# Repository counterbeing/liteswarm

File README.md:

## 2023-09-08 NOTE
this branch is a merge from a separate repo 100ideas/scarfswarm/releases/tag([BM23](https://github.com/100ideas/scarfswarm/releases/tag/BM23)|[v0.1.0](https://github.com/100ideas/scarfswarm/tree/v0.1.0)) which itself was refactored from [the 2019-july master branch of this  repo counterbeing/liteswarm, somewhere around here](https://github.com/counterbeing/liteswarm/blob/dc4e0e53ea9b77c02f954a00a81d340e21b89678/src/main.cpp). This branch compiles on esp32 dev boards with nrf24 and rotary encoder knobs attached to esp32 GPIO pins as defined in [`/src/config.h`](src/config.h). 

The GPIO pin settings should be compatible with ESP-WROOM-32 DevKit-v1 style breakout boards. I used these "[5PCS ESP-WROOM-32 ESP32 ESP-32S Development Board...](https://www.amazon.com/dp/B0BK13HWBJ) from amazon, but I want to switch to using one of the boards made by [Unexpected Maker](https://unexpectedmaker.com/shop.html) (tbd)."

I forked and old commit of the master branch, back when it was reliably working on arduino teensy in july 2019, and refactored it until it worked on esp32. Note, I have not verified that it STILL works on arduino teensy, so we should add a tag to the old master at a commit that was good on teensy, maybe around here https://github.com/counterbeing/liteswarm/blob/dc4e0e53ea9b77c02f954a00a81d340e21b89678/src/main.cpp. The most recent master commit before my merge from BM23 branch was https://github.com/counterbeing/liteswarm/tree/cc187bc9ed60972e2afc4fb52d72f6577941fd4b.

I started a new repo for my development work, [100ideas/scarfswarm](https://github.com/100ideas/scarfswarm).

## about
continutation of code developed with @counterbeing in https://github.com/counterbeing/liteswarm. `BM23` (and `master` currently) branch here is a minimal refactor of the teensy/arduino-compatible master branch of the liteswarm repo from 2019. Multiple contributors attempted to refactor or rearchitect the liteswarm code for esp32 but I couldn't get any of those branches to run. This branch does run on esp32, but it is not fancy. In fact, the code is ugly. But it works. I will push it to a branch on counterbeing/liteswarm for posterity. This repo is intended to be the home of scarfswarm FOSS firmware and hardware based on esp32, contributed by 100ideas and others.

To compile and upload this code onto an ESP32, use platformio in vscode. Once the platformio extension is activated, it should automagically configure a local gcc toolchain, download the project dependencies (`fastled/FastLED@^3.5.0`, `dparson55/NRFLite@^3.0.3`, `madhephaestus/ESP32Encoder`, `thomasfredericks/Bounce2@^2.55`, and all the magic contained in the `framework = arduino` line of `platformio.ini`), and compile them for esp32. If you encounter trouble building, try disabling `gcc` warnings by using a `platform.ini` similar to below (specifically `build_unflags` line):
```ini
[env:esp32dev]
platform = espressif32
board = esp32dev
framework = espidf
upload_port = /dev/cu.SLAB*
monitor_port = /dev/cu.SLAB_USBtoUART
monitor_speed = 115200
; esp32_exception_decoder is an add-on that parses kernel panic messages on serial such that error codes
;   and memory locations / program counter numbers are replaces with src code coordinates - handy!
monitor_filters = default, esp32_exception_decoder
; fix vendor-default extreme error setting in GCC (example code won't compile)
;   by disabling all gcc warnings
;   https://community.platformio.org/t/disable-warning-errors/13280/3
build_unflags = -Werror=all
; in extreme cases you may need to mess with how the linker/compiler resolves dependencies, try:
; lib_ldf_mode = chain+
```

**END 2023-09-08 NOTE**
---

## Swarming LEDs for LED Fun
This project can be be applied to many projects. Our prototype has been in scarves. These can also go in all sorts of other places:

- Wearables such as scarves and hats.
- Bike safety helmet.
- Bike lights.

### Why these? What's the swarm?
The thing that makes this project unique is the swarm. We're working to establish a way for multiple projects to communicate so that you can sync up animations with friends or even strangers.

Cheap simple hardware that can be put together in a robust and ad-hoc way to
keep you safe for nights of partying, or bicycling. Keep your friends all in a group with a synchronized mobile light show.

### Materials / Shopping List
These are some of the materials we've used to build our own. You can pretty much bank on them workin for your project.
- [portable battery packs](https://smile.amazon.com/Smallest-Jackery-3350mAh-Portable-Charger/dp/B00L9F95RO/ref=sr_1_8?keywords=jackery+battery+pack&qid=1559954560&s=gateway&sr=8-8), not a bad idea to have two. These are small enough to fit inside of a fuzzy scarf, and they don't turn off on you. You can get a few hours out of one of these... Depends on the animation you run. *mac likes Jackery if you can find 6000-12000mAh capacity for less than $20)
- another batt option [PowerAdd Slim 2 5000 mAh Compact Battery Packs](https://www.amazon.com/dp/B00KG45W08) ($13)
- [fabric](https://www.joann.com/luxury-faux-husky-fur-fabric--white/14387674.html)
- [arduino nanos](https://smile.amazon.com/gp/product/B07HF5RMHV/ref=crt_ewc_title_dp_2?ie=UTF8&psc=1&smid=A278BT9THV444Y)
- [led strips](https://www.aliexpress.com/item/5m-5V-WS2812B-WS2812-Led-Strip-light-Individually-Addressable-Smart-RGB-Led-pixel-strips-Black-White/32995915537.html?spm=a2g0o.cart.0.0.69a03c00Io4CfT)
- moar strips [WS2811](https://hackmd.io/@100ideas/scarfswarm#LED-strips) (see hackmd doc below for links to Ray Wu's led store)
- [usb cables](https://www.amazon.com/HTTX-Straight-Soldering-Connector-Replacement/dp/B07D1HDJM8/ref=sr_1_10?keywords=usb-a+connector+male&qid=1559956539&s=gateway&sr=8-10)
- [rotary encoder](https://smile.amazon.com/DIYhz-Rotary-Encoder-Digital-Potentiometer/dp/B07D3D64X7/ref=sr_1_10?keywords=rotary+encoder&qid=1559955080&s=industrial&sr=1-10)
- [wire](https://www.amazon.com/StrivedayTM-Flexible-Silicone-electronic-electrics/dp/B01KQ2JNLI/ref=sr_1_8?keywords=soldering+wire&qid=1559956794&s=gateway&sr=8-8)
- [nRF24L01+ 2.4 Ghz radio](http://a.co/d/3rhLgCT)
- Bourns PEC11 12mm 24-pulse rotary encoder (PEC11-4215F-S24) [adafruit #377](https://www.adafruit.com/product/377) ($4.50/1); [datasheet](https://cdn-shop.adafruit.com/datasheets/pec11.pdf) (need 10x)
- [usb type a male adapter 20-pack]( https://www.amazon.com/gp/product/B07GGJGB7Q) ($11) (for making power cables)
- [JST 4pin male-female connector pigtails, pack of 20](https://www.amazon.com/gp/product/B075K3M1TB) ($11)
- [112Pcs 2.54mm Male and Female Pin Header Connector Assortment Kit, 100pcs Stackable Shield Header](https://www.amazon.com/gp/product/B07CWSXY7P) ($13)
- [Capri Tools 20011 Automatic Wire Stripper and Cutter
](https://www.amazon.com/gp/product/B01018CX46) ($14) - get one. changed my life.

[
Scarfswarm / bikelights Big Red animation demo (youtube 2m)](https://youtu.be/5sAtdrZpyJc)

## Contributing
### Getting Involved
If you'd like to submit a bug, go ahead and use the issue tracker.

If you'd like to make submit a feature or a fix.
  - Open an issue to get buy in.
  - Fork the repo.
  - Make your changes.
  - Submit a pull request.

### Troubleshooting
Things you might be missing.
- edit using VSCode with PlatformIO plugin
- OpenOCD some USB stuff `brew install openocd` (or else `dyld: Library not loaded: /usr/local/opt/libftdi/lib/libftdi1.2.dylib`)

## Reference
**project documentation** https://hackmd.io/@100ideas/scarfswarm

libraries we're using:
- [FastLED.h](https://github.com/FastLED/FastLED) let their be light
- [NRFLite.h](https://github.com/dparson55/NRFLite) ... longwave light
- arduino / teensy [SPI](https://www.pjrc.com/teensy/td_libs_SPI.html) library
- [Encoder](https://github.com/PaulStoffregen/Encoder) - performant quadrature encoder for rotary inputs
- 

---

## 2019-12-12 Teensy-LC + NRF24L01+ notes

teensy forum faq: https://forum.pjrc.com/threads/25395-Teensy-Quick-Reference-Code-Examples-Tips-and-Tricks?highlight=nrf24l01
- also see
  - getting 128-bit ID hardcoded into chip
  - interval timer using interrupts
  - simple task library
  - libs https://www.pjrc.com/teensy/td_libs.html
    - debounce
    - timers

Optimized High Speed NRF24L01+
- https://tmrh20.github.io/RF24/
- mentioned on pjrc forums https://forum.pjrc.com/threads/40499-Need-to-change-SPI-clock-rate-for-RF24-radio-modules-w-TMRh20-library

NRF24L01+ w/ amazon breakout boad diagram
-----------------------------------------------------------------------------------------------

                                                 (pins)       NRF24L01+ breakout board pcb
    | nrf:teensy pin# | nrf:teensy     |      |-----------------------------------------------|
    | --------------- | -------------- |      |[1] | 2  |                      (antenna)      |
    | 1: GND   GND    | 2: VCC  (+3.3v)|      | -- | -- |        -------     ===============  |
    | 3: 9     CE     | 4: 10?  CSN    |      | 3  | 4  |        | C H |        ||   -----||  |
    | 5: 13    SCK    | 6: 11   MOSI   |      | -- | -- |        | I P |        ||   ||-----  |
    | 7: 12    MISO   | 8: ?    IRQ    |      | 5  | 6  |        -------        ||   -----||  |
                                              | -- | -- |                       ||   ||-----  |
                                              | 7  | 8  |                       ||   -----||  |
    Functions as follows:                     |---------|                            ||-----  |
    1: Ground                                 |         ( 16.000 )                        ||  |
    2: Vcc (3.3v)                             |-----------------------------------------------|
    3: CE (Chip Enable)
    4: CSN (Chip Select Not) Active Low - SPI Chip Select function
    5: SCLK (Clock) - SPI Clock Function
    6: MOSI (Master Out Slave In) - SPI Data
    7: MISO (Master In Slave Out) - SPI Data
    8: IRQ (Interrupt) - Optional, but goes low to indicate that data has arrived, fault has
       occurred, or write buffer full.

> SPI has 4 signals: **SS**, **SCK**, **MOSI**, **MISO**. SCK is a clock signal. Master Out Slave In (MOSI) sends data from the SPI master to one or more slaves. Master In Slave Out (MISO) is how slaves send data back to the master. To talk to only one of several slaves, the Slave Select (SS) pin is used. Thus, some chips need only 3 or even 2 of these signals; a display, for example, will use MOSI but not MISO, as it is an output only device.
>
> Multiple SPI devices use the same SPI SCK, MISO and MOSI signals but each device will need it's own SS pin.

| Signal | Function      | Teensy 2.0 | Teensy++ 2.0 | Teensy 3+ / LC * | ALT Teensy 3+ / LC |
| ------ | ------------- | ---------- | ------------ | -------------- | ------------------ |
| SS     | Select device | 0          | 20           | 10             | -                  |
| SCK    | Clock         | 1          | 21           | 13             | 14                 |
| MOSI   | Data Output   | 2          | 22           | 11             | 7                  |
| MISO   | Data Input    | 3          | 23           | 12             | 8                  |

\* these pins are set by default by SPI library(?). To use ALT, make calls to `SPI.setMOSI(pin)` etc.

> However, the SS pin must either be configured as an output, or if it is an input, it must remain low during the SPI transfer. Unconfigured pins default to input, and a pin with no signal can easily "float" to random voltages due to electrical noise. Always configure the SS pin as an output, or make sure it remains low.
>
> Sometimes, the SPI pins are already in use for other tasks when an SPI device is added to a project. If that task is simply a digital pin, or an analog input, it is usually better to move that to another pin so that the hardware SPI can be used. Sometimes though, the conflicting pin cannot be moved. The Audio Adapter, for example, uses some of the SPI pins to talk to the Audio DAC over I2S. For this case, Teensy 3.x provides an alternate set of SPI pins.
>
> The main SPI pins are enabled by default. SPI pins can be moved to their alternate position with SPI.setMOSI(pin), SPI.setMISO(pin), and SPI.setSCK(pin). You can move all of them, or just the ones that conflict, as you prefer. The pin must be the actual alternate pin supported by the hardware, see the table above; you can't just assign any random pin.

https://www.pjrc.com/teensy/td_libs_SPI.html

-----------------------------------------------------------------------------------------

## dont overflow if counting packets...
how many packets (max) could a device see per second?
```
(800kbps * 1 second) / 32 bytes = 3125
(2MBps * 1 second) / 32 bytes   = 62500
```
see UINT_MAX from std::numeric_limits 
- https://en.cppreference.com/w/cpp/types/climits
- https://en.cppreference.com/w/cpp/types/integer

| uint sizes | atmel / arduino | teensylc arm cortex M0 |
| ---------- | --------------- | ---------------------- |
| INT8_MAX   | 127             |                        |
| UINT8_MAX  | 255             |                        |
| INT16_MAX  | 32767           |                        |
| UINT16_MAX | 65535           |                        |
| INT32_MAX  | 2147483647      |                        |

```c
// https://www.badprog.com/c-type-what-are-uint8-t-uint16-t-uint32-t-and-uint64-t

// testValue
unsigned long long testValue     = 0xFFFFFFFFFFFFFFFF; // 18446744073709551615

// 1 byte -> [0-255] or [0x00-0xFF]
uint8_t         number8     = testValue; // 255
unsigned char    numberChar    = testValue; // 255

// 2 bytes -> [0-65535] or [0x0000-0xFFFF]
uint16_t         number16     = testValue; // 65535
unsigned short    numberShort    = testValue; // 65535

// 4 bytes -> [0-4294967295] or [0x00000000-0xFFFFFFFF]
uint32_t         number32     = testValue; // 4294967295
unsigned int     numberInt    = testValue; // 4294967295

 // 8 bytes -> [0-18446744073709551615] or [0x0000000000000000-0xFFFFFFFFFFFFFFFF]
uint64_t             number64         = testValue; // 18446744073709551615
unsigned long long     numberLongLong    = testValue; // 18446744073709551615
```

## deviceId collisions
calculate liklihook of id collisions, where n = number of devices & d = keyspace size (using birthday problem formula):

1 - (d!) / ((d - n)! * d^n)

n = 10 devices
d = 256 (uint_8)
p = 16%

n = 10 devices
d = 32768 (uint_16)

### 2019-11-21 dev notes for scarfquest
intellisense not picking up uintxx types from `/Users/100ideas/.platformio/packages/toolchain-atmelavr/avr/include/stdint.h`

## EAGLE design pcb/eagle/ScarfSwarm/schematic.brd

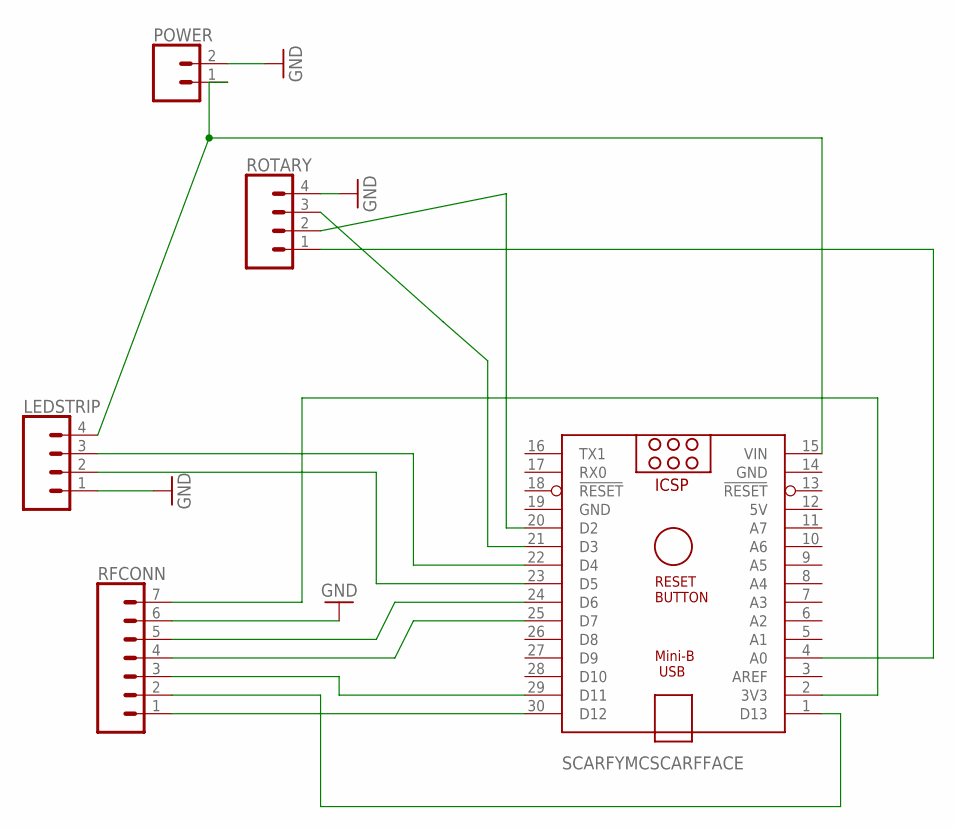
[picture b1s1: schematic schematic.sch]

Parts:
LEDSTRIP: CONN_04PTH; 1X04
POWER: CONN_02LOCK_LONGPADS; 1X02_LOCK_LONGPADS
RFCONN: CONN_07; 1X07
ROTARY: CONN_04PTH; 1X04
SCARFYMCSCARFFACE: ARDUINO_NANO

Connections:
5V: SCARFYMCSCARFFACE.12 (5V)
GND: LEDSTRIP.1, POWER.2, RFCONN.6, ROTARY.4, SCARFYMCSCARFFACE.14 (GND), SCARFYMCSCARFFACE.19 (GND)
unnamed: RFCONN.7, SCARFYMCSCARFFACE.2 (3V3)
unnamed: RFCONN.5, SCARFYMCSCARFFACE.24 (D6)
unnamed: RFCONN.4, SCARFYMCSCARFFACE.25 (D7)
unnamed: RFCONN.2, SCARFYMCSCARFFACE.1 (D13)
unnamed: RFCONN.3, SCARFYMCSCARFFACE.29 (D11)
unnamed: RFCONN.1, SCARFYMCSCARFFACE.30 (D12)
unnamed: LEDSTRIP.2, SCARFYMCSCARFFACE.23 (D5)
unnamed: ROTARY.3, SCARFYMCSCARFFACE.21 (D3)
unnamed: ROTARY.2, SCARFYMCSCARFFACE.20 (D2)
unnamed: ROTARY.1, SCARFYMCSCARFFACE.4 (A0)
unnamed: LEDSTRIP.4, POWER.1, SCARFYMCSCARFFACE.15 (VIN)
unnamed: LEDSTRIP.3, SCARFYMCSCARFFACE.22 (D4)

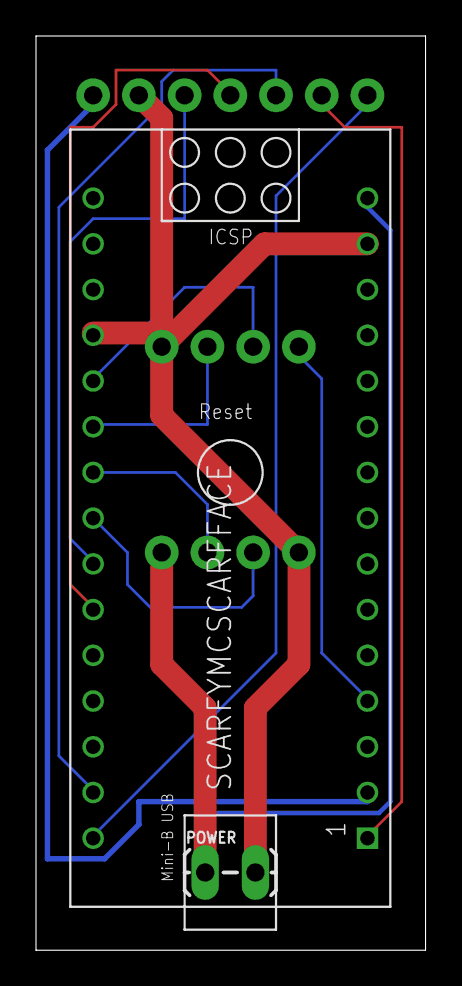
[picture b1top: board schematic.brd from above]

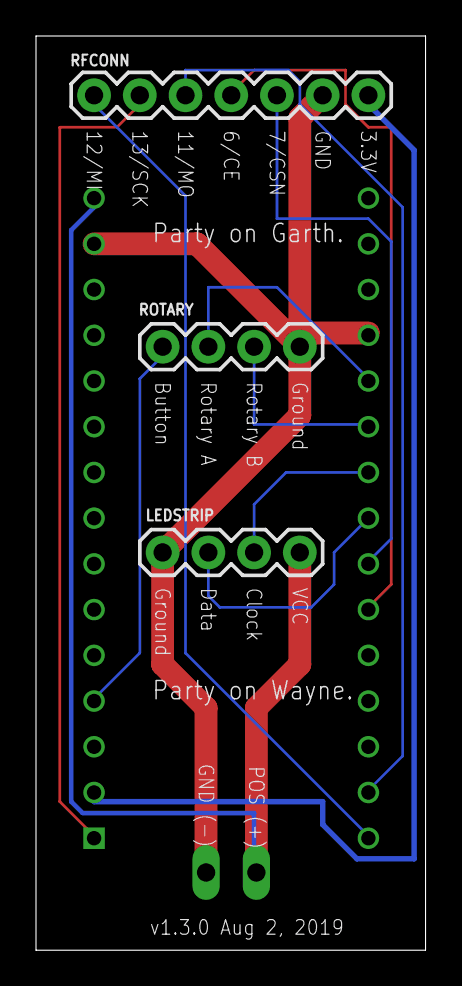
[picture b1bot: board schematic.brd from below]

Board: 2 copper layers, 21.6 x 50.8 mm, 5 parts (3 on the bottom side), 13 nets.

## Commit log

2016-08-07 initial working
2016-08-07 add debouncer
2016-08-08 reading rotary
2016-08-08 adjust animation speeds
2016-08-08 add some animations
2016-08-15 performance adjustments
2016-08-15 unblock strobe call
2016-08-16 add crossfade back in
2016-08-25 add snakes on a plane
2017-09-08 playa hacks to strandtest.ino for longer lengths
2017-09-08 add documentation folder
2017-09-09 pinouts & datasheets
2019-06-06 trying out an ide
2019-06-07 reorder some things
2019-06-07 got it compiling and uploading
2019-06-07 code is messed up, updates to readme
2019-06-07 problematic
2019-06-07 reg error
2019-06-07 this compiles with knob logic extracted to h file
2019-06-07 tweakls
2019-06-07 tinker
2019-06-07 kind of working... with mac
2019-06-07 closer to working
2019-06-07 a slightly buggy branch
2019-06-07 remove unnecessary variable from circulation
2019-06-07 some kinda fix, whew, we tired
2019-06-07 Things are working as of now.
    - Removed Serial comments
    - Race now does what color slide once did
    - Color slide is no longer included as it was buggy
    - No plans to reimplement race as it was originally, never really liked
    it all that much.
2019-06-07 Cleanup.
    - Added debugging note
    - Removed stale comments and code
    - Adjusted pixel value using debug technique
    We could potentially stick that NUMPIXELS into an env var or something,
    but for now, it's here.
2019-06-08 Add list of materials
2019-06-08 Added a new animation to choose your own color
2019-06-08 color chooser doesn't quite work for some reason
2019-06-08 It's in working order, but no color chooser
    Interestingly there are problems if i change the order of the case
    statement, I have no idea why.
2019-06-16 Added looping ability.
    This is mostly for color chooser, which still causes some kind of other
    crash. Still working that out, if you want to try it out feel free to
    comment out the switch statment and just run the color chooser
    animation.
2019-06-17 moved basic animation to class
2019-06-17 knob receives defaults from animation instance
2019-06-17 added crossfade back in
2019-06-17 diamond necklace runs as intended
2019-06-17 added fuck my eyes
2019-06-17 major cleanup
2019-06-17 dotstar lib is now gone
2019-06-17 moving animations to folder and more cleanup of old vars
2019-06-17 Use pointers to reference animations
    Rather than using the run function directly from the instance of the
    animation, we use a pointer. This allows us to call the setup function
    once for each animation without repeating it over and over.
2019-06-17 tweaks and cleanup
2019-06-17 for whatever reason this order works, not sure why
2019-06-17 slightly faster defualt intervals for a couple of animations
2019-06-19 temp change to ws2811
2019-06-22 very literal move of code not working yet
2019-06-23 almost working basic RF
2019-06-23 this works
2019-06-23 keyframe note
2019-06-26 these sync with animation and rotary
2019-07-08 Fixes for jittery changes when using rotary
    Previously all parties tried to broadcast constantly, this could turn
    into a feedback loop. Here we prevent the broadcast of a packet unless
    there is a manual change that needs broadcasting.
    Also add a sync period.
2019-07-26 with rainbow animation
2019-07-26 add initial schematic
2019-07-26 try trimming off th external componetns, first board layout
2019-07-27 add auto routing with pads on back
2019-07-28 swapped out arduino lib, still have errors
2019-07-28 add libs
2019-07-30 v1 of boards
2019-07-30 add a little more beef to some of the power lines
2019-07-30 v1.1 Fatten some of the leads
2019-07-31 scarfymcscarfface
2019-07-31 silk screen change
2019-08-02 reorder radio contacts so that they are easy to solder
2019-08-02 tidy schematic slightly
2019-08-02 remove old backup
2019-08-06 update for PCB use
2019-08-06 rearrange JST connection for strip, bump version
2019-08-07 reorder animations and tighten rainbow
2019-08-07 hold actions are now printed to serial
2019-08-07 code cleanup
2019-08-08 there is now an off mode
2019-08-08 add stripes animation
2019-08-08 a couple more animations
2019-08-08 clarify comment
2019-08-13 add scarf-diagram, gitignore .vscode
2019-08-13 configs for mac protoboard + breadboard
2019-08-14 partially done w/ knob combo detection
2019-08-14 think the combomatcher logic is starting to work
2019-08-14 combo logic seems good + great var names
2019-08-14 cleaned up code, looks good! next up dispatch
2019-08-14 comboPattern string -> switch case dispatcher works
2019-08-14 FIX swapped pin bug CS<->CSM v1.3; SK9822 BGR order
2019-08-14 cmdMode starts after med->short combo
2019-08-14 kinda-working off mode
2019-08-14 offmode more stable but no feedback
2019-08-14 printf.h printf() -> serial helper lib
2019-08-18 testing cedux, running out of space
2019-08-21 add ws comment
2019-08-22 change strip to WS and flip data and clock
2019-08-22 ws2815 working; clang format rule; more mem less serial
2019-08-22 updated log
2019-08-22 getting ifdefs for config.h
2019-08-22 rebased master
2019-08-22 autoformat all google clang style
2019-08-23 centralize FastLED.show()
2019-08-23 update debug var names, and update readme
2019-08-23 ignore packets without a secret
2019-08-23 do not begin transmitting immediately on launch
2019-08-23 cap brightness of dimmer to prevent 1A power source failure
2019-08-24 adding basic feedback to command mode
2019-08-24 add dotstar
2019-08-24 not working yet
2019-08-24 pass by ref works
2019-08-24 moving to global state
2019-08-26 don't n=know post camp setup
2019-09-03 on-playa hacking for bigred strips
2019-09-05 disable cmdmode === bar demo FTW
2019-10-19 🐛 Fix config issue
    This issue seems to be caused by comments after the values. This used to
    work, but after a PIO update, no longer does.
2019-10-25 add logo art
2019-10-25 🌈 logo for readme
2019-10-25 swap out animation reference
2019-10-25 add lightning animation, is now just green
2019-10-25 fix issue with VSCode misreporting error
2019-10-25 a fairly convincing lighting bug fade
2019-10-25 get rid of signing warning
2019-10-31 working for ws short strands
2019-10-31 making a bit of a mess, but the lighting-butt animation now works as intended
2019-11-21 ustd lib (maps) not config correct
2019-11-21 tixed (hopefully) intellisense bug complaining about missings nested deps
2019-11-21 ustd/map.h lib working; intellisense fixed
2019-11-21 initial SwarmMap activity logic
2019-11-22 cant figure out how to pass SwarmMap to radio
2019-11-22 ustd::map.remove() doesnt remove
2019-11-22 SwarmMap can provide list/count of active swarm
2019-11-22 playing w/ locking in lightning-butt
2019-11-26 replaced off mode with strobe mode
2019-12-01 bunch of refactoring
2019-12-02 bunch of refactoring 2
2019-12-02 clean up
2019-12-02 move leds member into base Animation class
2019-12-03 streamlined button events; off mode now uses long click
2019-12-03 simplified knob configured settings; added startup sequence
2019-12-03 animations extend base controller
2019-12-03 collapse KnobControl into KnobSetting
2019-12-03 include cleanup
2019-12-04 startup sequence fix
2019-12-04 fixed radio send; ALSO BROKEN LEDS ON ANIMATION LOOP (hangs when animationIndex goes back to zero)
2019-12-04 fixed animationIndex reset bug
2019-12-08 makes esp32 work with test pattern
2019-12-08 🤖 set up clang-formatter
    If this is trouble feel free to revert it, i just think it might save us
    some pain later.
2019-12-08 radio receiving now works; made constants const
2019-12-13 modify config for teensylc
2019-12-13 sigh reduced to pathetic blinkyled debugging
2019-12-13 teensy leds working, not radio
2019-12-13 found possible buffer overflow in rotaryPosition + radio
2019-12-13 standardizing rotaryposition to int16 (32767)
2019-12-13 refactoring buttonPosition to int16_t
2019-12-13 bugs everywhere! teensy not liking radio
2019-12-13 wrote up debug log; nano scarves work ok
2019-12-13 update readme, debug journal, teensy pinout pic
2019-12-13 update readme, teensy debug journal, teensy pio env
2019-12-13 add info on pragma pack
2019-12-13 fix table formatting
2019-12-17 struct members big to small to avoid padding
2019-12-19 hacky fix of knob.confine update loop bug
2019-12-19 avoid crash caused by anim_index 0
2019-12-19 fix filename date
2019-12-19 add teensy kicad pcb rev 1
2019-12-28 initial xy matrix mapped animation
2019-12-28 knob changes color of Rider animation
2019-12-28 hacking multiparam knob for Rider
2019-12-28 unworking
2020-11-01 got it compiling again
2020-11-01 rejigger ini config
2020-11-01 adjust clang format
2020-11-01 run clang format everywhere
2020-11-01 configuring workspace recommendations
2020-11-02 version for encoder lib
2020-11-11 use arduino framework on esp32
2020-11-11 moving config around
2020-11-11 streamline config
2020-11-11 split out includes
2020-11-12 fix conditional compilation
2020-11-12 wip: conditional bug where ESP32Encoder gets included for nano
2020-11-12 replace guard clauses with pragma once
2020-12-03 at long last, she builds
2020-12-03 tweaks
2020-12-03 animationModeConroller gets pointer to state
2020-12-04 iterate
2023-09-09 init manual fork of 100ideas/scarfswarm/releases/tag/BM23
2023-09-09 Update README.md
    add commit links to readme to help find teensy-compatible master commits

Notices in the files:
parts and their libraries:
SparkFun-Connectors: Licensing: Creative Commons ShareAlike 4.0 International - https://creativecommons.org/licenses/by-sa/4.0
